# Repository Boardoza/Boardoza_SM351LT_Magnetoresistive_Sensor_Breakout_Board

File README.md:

# Boardoza SM351LT Magnetoresistive Sensor Breakout Board

The **Boardoza SM351LT** is a high-sensitivity **magnetoresistive sensor module** designed for lid, door, and drawer position detection. It features **omnipolar sensing**, activating with either pole of a magnet. With a **push-pull output**, the module eliminates the need for an external pull-up resistor, simplifying integration into various applications.

## [Click here to purchase!](https://www.ozdisan.com/maker-ve-iot-urunleri/boardoza/boardoza-modulleri/BOARDOZA-SM351LT/1206518)  

| Front Side | Back Side |
|:---:|:---:|
|  |  |

---

## Key Features

- **Lid, Door, and Drawer Position Detection:** Detects open/closed states using a magnet.  
- **Non-Contact Operation:** Works through non-metallic surfaces, making it ideal for sealed enclosures.  
- **Omnipolar Sensing:** Responds to both north and south poles of a magnet for flexible placement.  
- **Push-Pull Output:** Built-in driver circuit eliminates the need for an external pull-up resistor.  
- **Dual LED Indicators:** Includes **Power Good LED (D1)** and **Output Indicator LED (D2)** for real-time status feedback.  

---

## Technical Specifications

**Model:** Honeywell SM351LT  
**Voltage Supply:** 3.3V - 5V  
**Voltage Input Type:** 3-pin 2.50mm header  
**Current Consumption:** 150µA  
**Sensor Type:** Magnetoresistive Sensor  
**Output Type:** Push-Pull (No external pull-up required)  
**Operate Sensing Range:** Typical: 7 Gauss  
**Operating Temperature:** -40°C to +85°C  
**Board Dimensions:** 20mm x 20mm  

---

## Board Pinout  

| Pin Number | Pin Name | Description |
|:---:|:---:|---|
| 1 | VCC | Power Supply (3.3V - 5V) |
| 2 | OUT | Digital Output (Push-Pull) |
| 3 | GND | Ground |

---

## Board Dimensions  

---

## Step Files  

[Boardoza SM351LT.step](./assets/SM351LT%20Step.step)

---

## Datasheet  

[Boardoza SM351LT Datasheet.pdf](./assets/SM351LT%20Datasheet.pdf)

---

## Version History  

- V1.0.0 - Initial Release  

---

## Support  

- If you have any questions or need support, please contact **<support@boardoza.com>**  

---

## License  

Shield: [![CC BY-SA 4.0][cc-by-sa-shield]][cc-by-sa]  

This work is licensed under a [Creative Commons Attribution-ShareAlike 4.0 International License][cc-by-sa].  

[![CC BY-SA 4.0][cc-by-sa-image]][cc-by-sa]  

[cc-by-sa]: http://creativecommons.org/licenses/by-sa/4.0/  
[cc-by-sa-image]: https://licensebuttons.net/l/by-sa/4.0/88x31.png  
[cc-by-sa-shield]: https://img.shields.io/badge/License-CC%20BY--SA%204.0-lightgrey.svg

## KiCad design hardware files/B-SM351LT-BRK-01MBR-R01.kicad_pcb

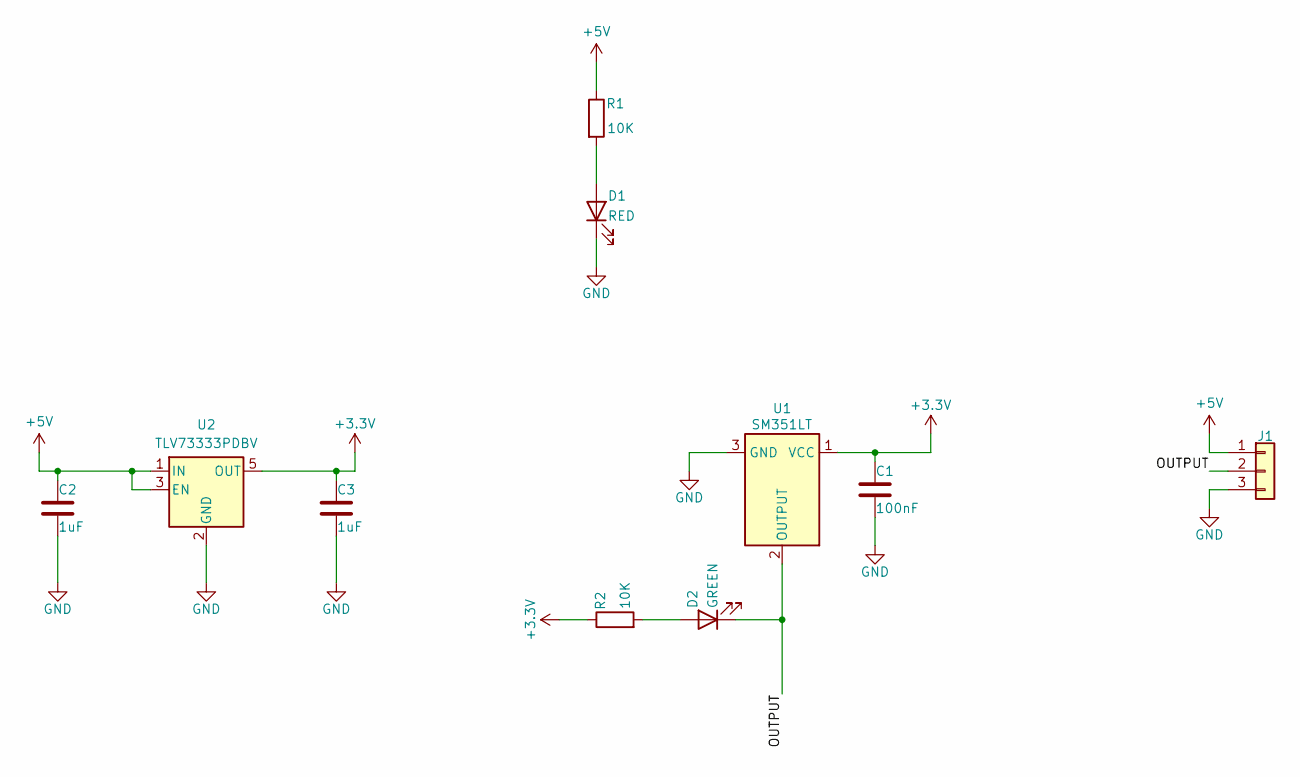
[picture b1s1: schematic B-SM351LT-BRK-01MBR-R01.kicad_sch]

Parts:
C1: 100nF; C_0603_1608Metric
C2, C3: 1uF; C_0603_1608Metric
D1: RED; LED_0603_1608Metric
D2: GREEN; LED_0603_1608Metric
J1: Conn_01x03; 2317-03S_1x03_P2.50mm_Vertical
R1, R2: 10K; R_0603_1608Metric
U1: SM351LT; SOT-23; MPN SM351LT
U2: TLV73333PDBV; SOT-23-5; MPN TLV73333PDBV

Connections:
+3.3V: C1.2, C3.2, R2.1, U1.1 (VCC), U2.5 (OUT)
+5V: C2.2, J1.1, R1.1, U2.1 (IN), U2.3 (EN)
/OUTPUT: D2.1 (K), J1.2, U1.2 (OUTPUT)
GND: C1.1, C2.1, C3.1, D1.1 (K), J1.3, U1.3 (GND), U2.2 (GND)
unnamed: D1.2 (A), R1.2
unnamed: D2.2 (A), R2.2

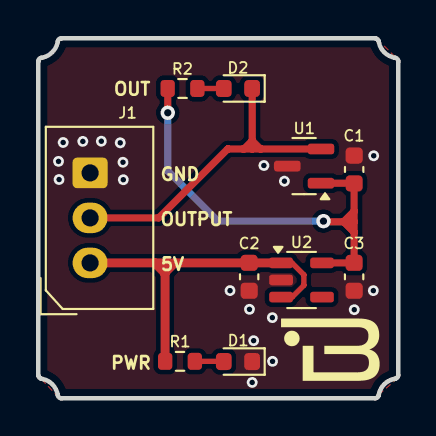
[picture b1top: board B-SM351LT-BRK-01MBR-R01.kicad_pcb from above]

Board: 2 copper layers, 20.0 x 20.0 mm, 10 parts (0 on the bottom side), 6 nets.

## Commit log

2025-03-19 Add initial documentation for Boardoza SM351LT
2025-03-19 Update README.md to enhance feature descriptions for Boardoza SM351LT
2025-03-19 Add voltage input type to README.md for Boardoza SM351LT
